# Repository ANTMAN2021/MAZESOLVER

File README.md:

# MAZESOLVER
1. A simple maze solver robot for competitions.
   Based on arduino uno, ultrasonic sensors and l298n motor driver.
2. Another similar robot with same code, with pcb and trials on STM 32.
   Shifted to Arduino in the end due to PWM channel issues.

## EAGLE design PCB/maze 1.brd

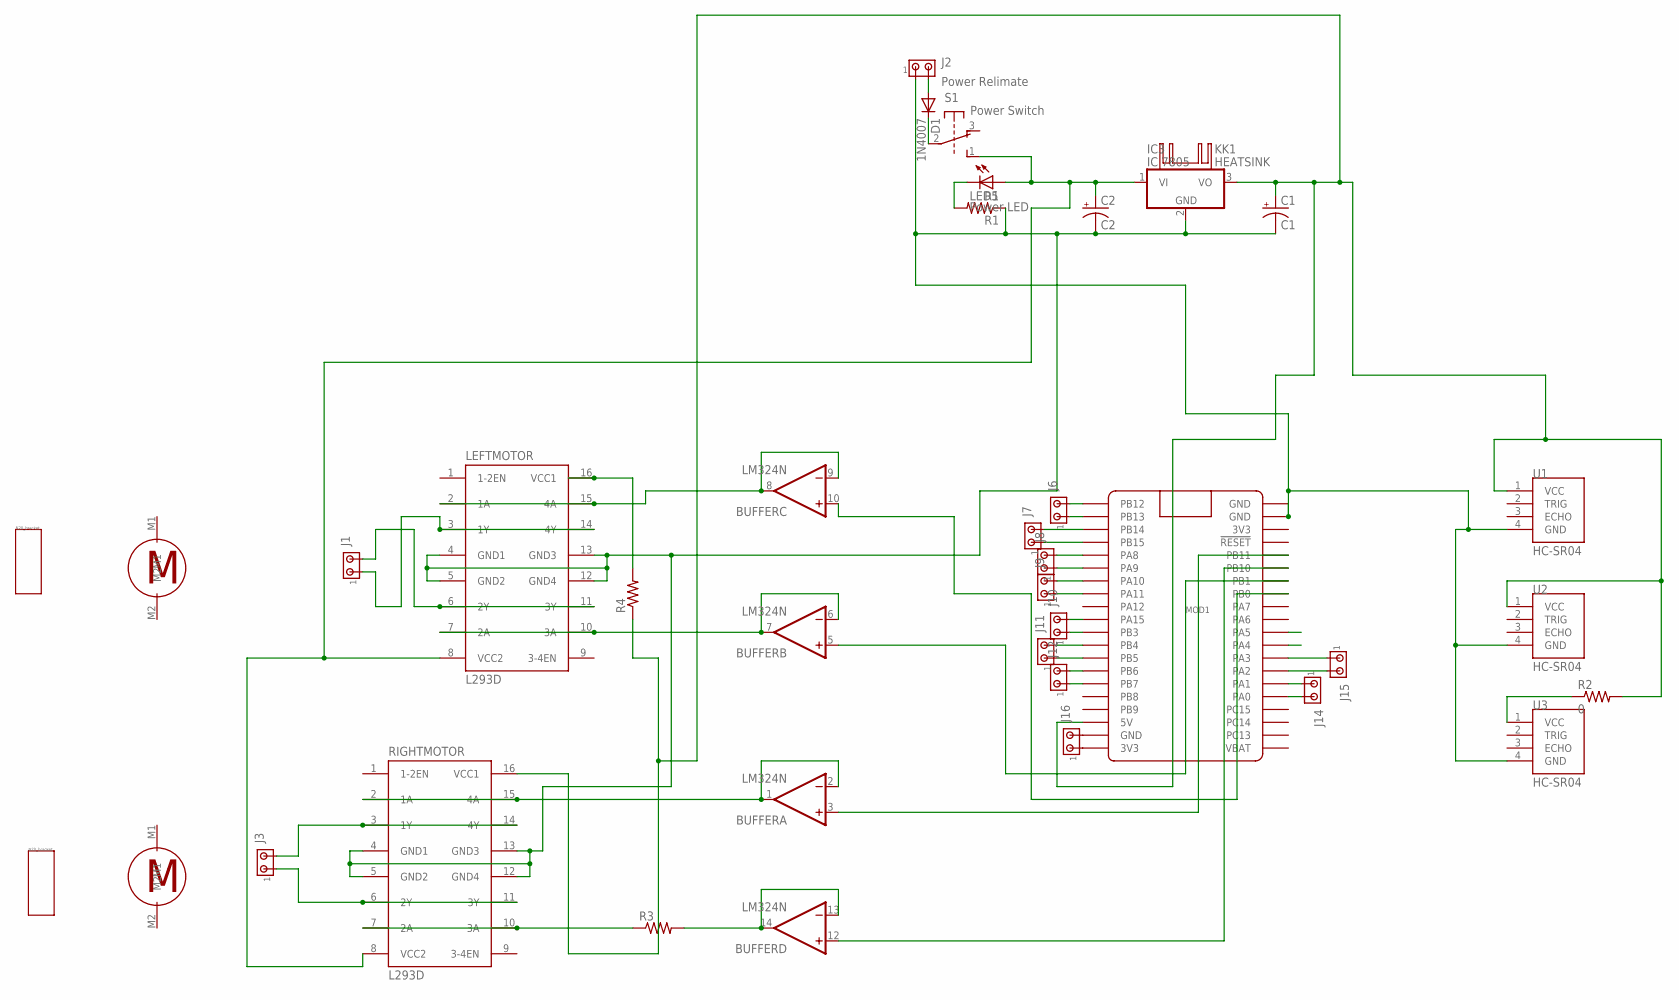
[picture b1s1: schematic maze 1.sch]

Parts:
BUFFER: LM324N; DIL14
C1: C1; CPOL-RADIAL-5MM-10MM
C2: C2; E3,5-8
D1: 1N4007; DO41-10
IC3: IC 7805; TO220V
J1, J3, J6, J7, J8, J9, J10, J11, J12, J14, J15, J16: MTA02-100; 10X02MTA
J2: Power Relimate; 10X02MTA
KK1: HEATSINK
LED5: Power LED; LED3MM
LEFTMOTOR: L293D; DIL16
MOD1: BLUE_PILL
R1: R1; 0204/7
R2: 0; 0204/7
R3, R4: R-US_0204/7; 0204/7
RIGHTMOTOR: L293D; DIL16
S1: Power Switch; 9077-2
U1, U2, U3: HC-SR04; XCVR_HC-SR04
U$1, U$2: MOTOR_N20
U$4, U$5: N20_BRACKET; BRACKER

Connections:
5V: BUFFER.4 (V+), C1.+, IC3.3 (VO), MOD1.P$18 (5V), R2.2, R4.1, RIGHTMOTOR.16 (VCC1), U1.1 (VCC), U2.1 (VCC)
12V: C2.+, IC3.1 (VI), LED5.A, LEFTMOTOR.8 (VCC2), RIGHTMOTOR.8 (VCC2), S1.1 (S)
GND: BUFFER.11 (V-), C1.-, C2.-, IC3.2 (GND), J2.1, LEFTMOTOR.4 (GND1), LEFTMOTOR.5 (GND2), LEFTMOTOR.12 (GND4), LEFTMOTOR.13 (GND3), MOD1.P$21 (GND), MOD1.P$22 (GND), R1.1, RIGHTMOTOR.4 (GND1), RIGHTMOTOR.5 (GND2), RIGHTMOTOR.12 (GND4), RIGHTMOTOR.13 (GND3), U1.4 (GND), U2.4 (GND), U3.4 (GND)
unnamed: BUFFER.12 (+IN), MOD1.P$26 (PB10)
unnamed: D1.A, J2.2
unnamed: BUFFER.5 (+IN), MOD1.P$27 (PB1)
unnamed: R2.1, U3.1 (VCC)
unnamed: J1.2, LEFTMOTOR.6 (2Y), LEFTMOTOR.11 (3Y)
unnamed: LED5.K (C), R1.2
unnamed: BUFFER.8 (OUT), BUFFER.9 (-IN), LEFTMOTOR.2 (1A), LEFTMOTOR.15 (4A)
unnamed: BUFFER.13 (-IN), BUFFER.14 (OUT), R3.2
unnamed: BUFFER.10 (+IN), MOD1.P$28 (PB0)
unnamed: D1.C, S1.2
unnamed: LEFTMOTOR.16 (VCC1), R4.2
unnamed: BUFFER.6 (-IN), BUFFER.7 (OUT), LEFTMOTOR.7 (2A), LEFTMOTOR.10 (3A)
unnamed: J1.1, LEFTMOTOR.3 (1Y), LEFTMOTOR.14 (4Y)
unnamed: BUFFER.3 (+IN), MOD1.P$25 (PB11)
unnamed: R3.1, RIGHTMOTOR.7 (2A), RIGHTMOTOR.10 (3A)
unnamed: J15.1, MOD1.P$33 (PA3)
unnamed: J15.2, MOD1.P$34 (PA2)
unnamed: J14.1, MOD1.P$35 (PA1)
unnamed: J14.2, MOD1.P$36 (PA0)
unnamed: J6.1, MOD1.P$2 (PB13)
unnamed: J6.2, MOD1.P$1 (PB12)
unnamed: J3.2, RIGHTMOTOR.3 (1Y), RIGHTMOTOR.14 (4Y)
unnamed: J7.2, MOD1.P$3 (PB14)
unnamed: BUFFER.1 (OUT), BUFFER.2 (-IN), RIGHTMOTOR.2 (1A), RIGHTMOTOR.15 (4A)
unnamed: J3.1, RIGHTMOTOR.6 (2Y), RIGHTMOTOR.11 (3Y)
unnamed: J7.1, MOD1.P$4 (PB15)
unnamed: J8.2, MOD1.P$5 (PA8)
unnamed: J8.1, MOD1.P$6 (PA9)
unnamed: J10.2, MOD1.P$10 (PA15)
unnamed: J10.1, MOD1.P$11 (PB3)
unnamed: J11.2, MOD1.P$12 (PB4)
unnamed: J11.1, MOD1.P$13 (PB5)
unnamed: J12.2, MOD1.P$14 (PB6)
unnamed: J12.1, MOD1.P$15 (PB7)
unnamed: J9.2, MOD1.P$7 (PA10)
unnamed: J9.1, MOD1.P$8 (PA11)
unnamed: J16.1, MOD1.P$20 (3V3)
unnamed: J16.2, MOD1.P$19 (GND)

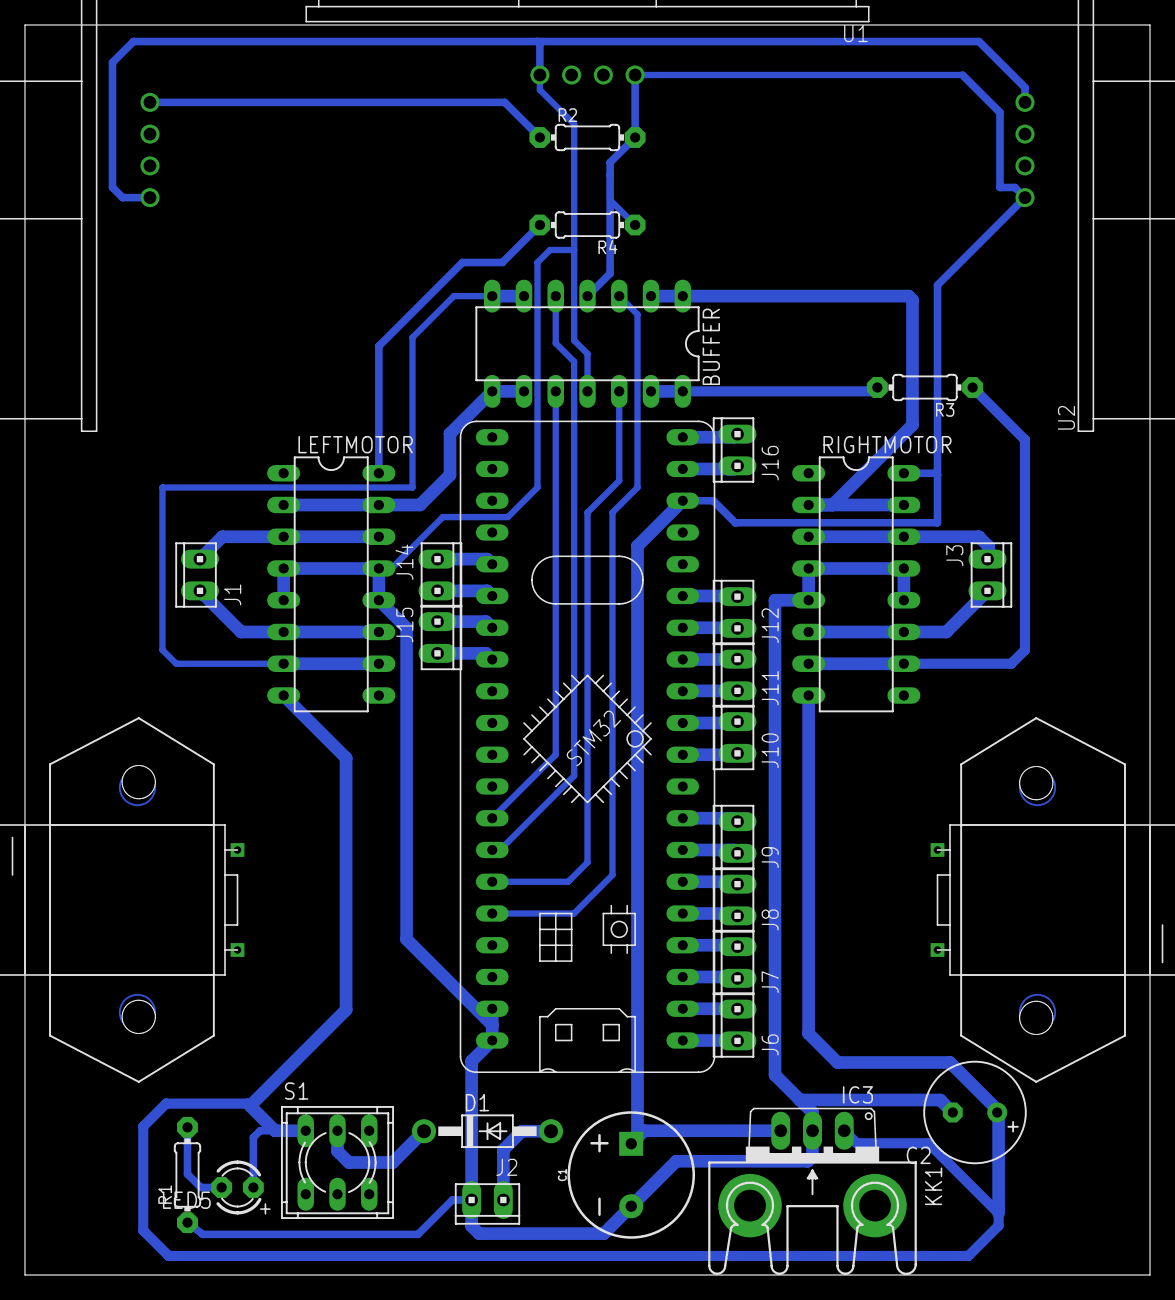
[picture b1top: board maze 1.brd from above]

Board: 2 copper layers, 90.0 x 100.0 mm, 35 parts (0 on the bottom side), 41 nets.

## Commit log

2024-08-04 Create PCB

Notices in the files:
parts and their libraries:
SparkFun-Capacitors: Licensing: Creative Commons ShareAlike 4.0 International - https://creativecommons.org/licenses/by-sa/4.0
heatsink: Copyright (C) 2004, Bob Starr (bobstarr@mindspring.com)
